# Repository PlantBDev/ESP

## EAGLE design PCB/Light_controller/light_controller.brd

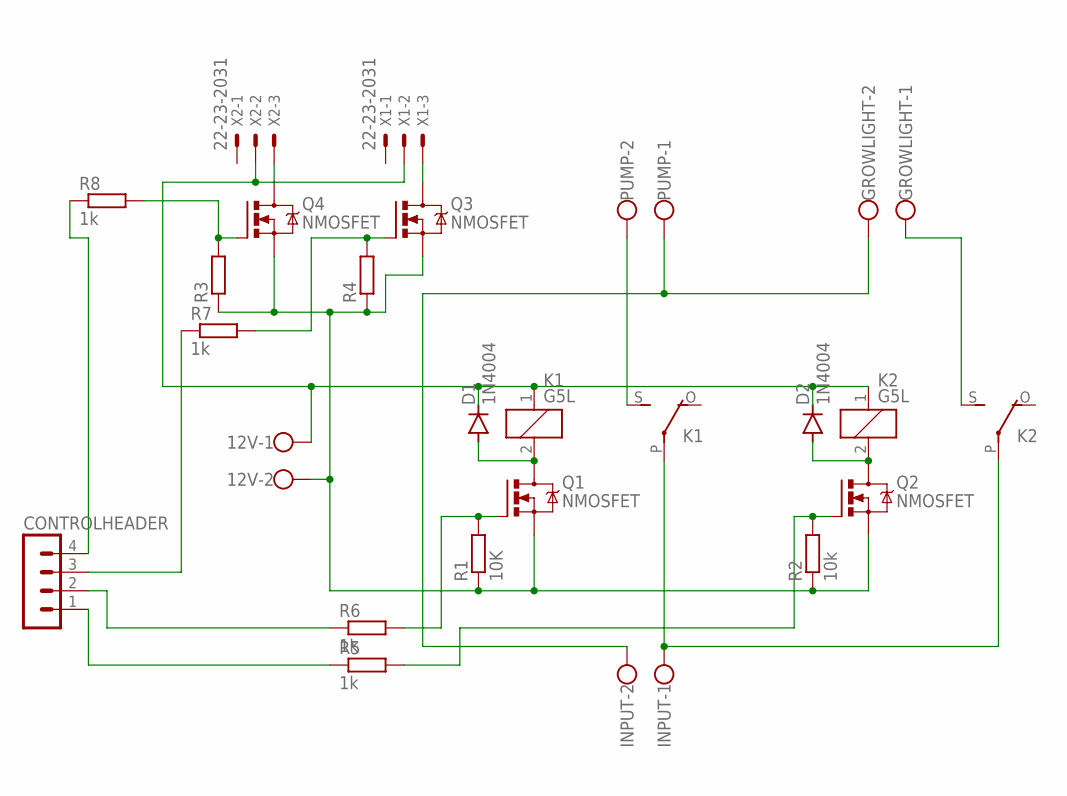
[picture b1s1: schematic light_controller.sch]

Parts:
12V: W237-102
CONTROLHEADER: MA04-1
D1, D2: 1N4004; DO41-10
GROWLIGHT: W237-102
INPUT: W237-102
K1, K2: G5L; G5LE
PUMP: W237-102
Q1, Q2, Q3, Q4: NMOSFET; TO220BV
R1: 10K; 0204/7
R2: 10k; 0204/7
R3, R4: R-EU_0204/7; 0204/7
R5, R6, R7, R8: 1k; 0204/7
X1, X2: 22-23-2031

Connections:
unnamed: D1.A, K1.2, Q1.D
unnamed: INPUT.1, K1.P, K2.P
unnamed: K1.S, PUMP.2
unnamed: GROWLIGHT.2, INPUT.2, PUMP.1
unnamed: 12V.1, D1.C, D2.C, K1.1, K2.1, X1.2, X2.2
unnamed: 12V.2, Q1.S, Q2.S, Q3.S, Q4.S, R1.1, R2.1, R3.1, R4.1
unnamed: Q1.G, R1.2, R6.2
unnamed: D2.A, K2.2, Q2.D
unnamed: Q2.G, R2.2, R5.2
unnamed: Q4.G, R3.2, R8.2
unnamed: GROWLIGHT.1, K2.S
unnamed: Q3.G, R4.2, R7.2
unnamed: CONTROLHEADER.1, R5.1
unnamed: CONTROLHEADER.2, R6.1
unnamed: Q4.D, X2.3
unnamed: Q3.D, X1.3
unnamed: CONTROLHEADER.3, R7.1
unnamed: CONTROLHEADER.4, R8.1

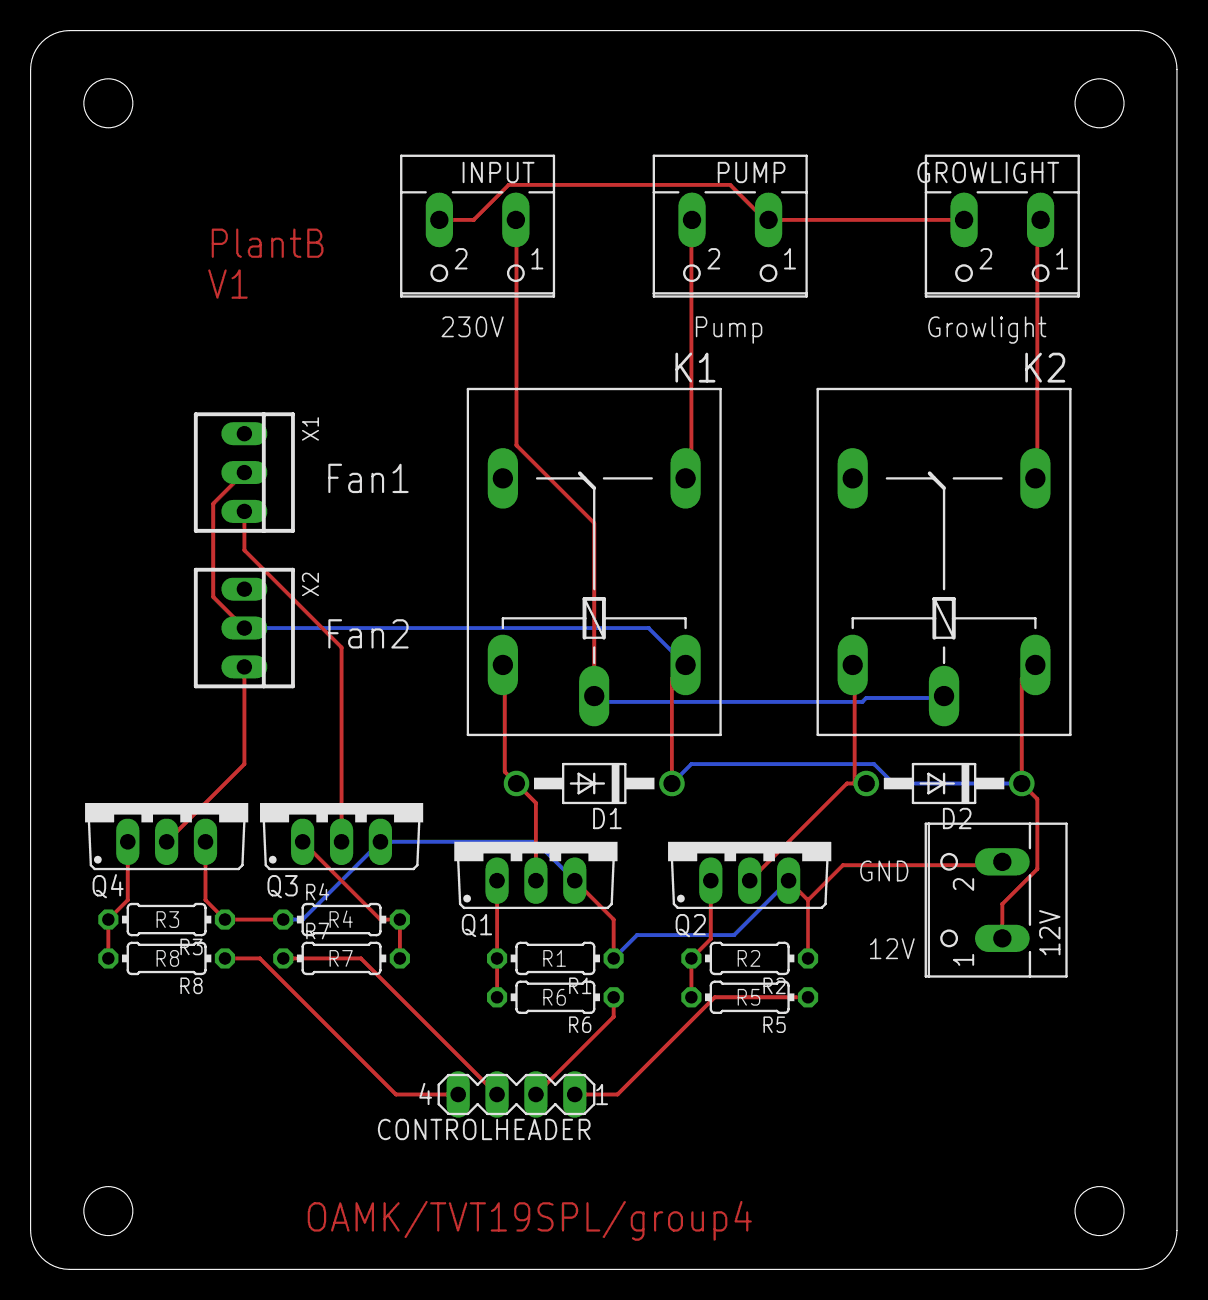
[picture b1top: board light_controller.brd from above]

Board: 2 copper layers, 74.9 x 81.0 mm, 23 parts (0 on the bottom side), 18 nets.

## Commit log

2021-03-23 Create text_print.py
    Python script to display text on the display in the control box. Still very work in progress
2021-03-23 Add files via upload
    This is my fan code
2021-03-23 Modified text_print to be callable
2021-03-23 NodeMainRevision2
    Basic mqtt fuctionality
2021-03-24 Added multi line prints
2021-03-25 Adressable line printing and image
    Added adrressable line printing and the possibility to display images. kukka.jpg is a placeholder logo image.
2021-03-26 WifiManager
    Steal customers wifi name and password and commit dastardly crimes with them
2021-03-31 PCB V1
    version 1 eagle files and gerber for pcb manufacturing
2021-04-07 Create nodeIdentifyv2.ino
    lol
2021-04-07 Added temperature sensor related documents
    Function to read sensors, function to convert data to temperature and octave file and documentation
2021-04-07 Added a function to read temperaturesensors
2021-04-07 Updated nodeMain to revision4
    nodeMain is currently in functioning state
2021-04-10 Add files via upload
    Here is the 3d-models for the plantB body
2021-04-11 Delete potHolderV4_Slim.FCStd
    removed broken model
2021-04-14 Update Waterlevel_sensor_v0.1.ino
    Added some emptyliensd
2021-04-18 NTP clock handler and example main for it
2021-04-18 Added Event timer
    Still very much incomplete
2021-04-19 Progress on event timer and use of sensorRequest
    eventTimer includes still some not so useful input variables
2021-04-21 NodeMainRev6
    6th revision of the main function
2021-04-22 I2C functions
    I2C for both Arduino and Node devices
2021-04-22 fixes to bad code
    yhyy
2021-04-22 various bug fixes
    code is testable, and in working condition
2021-04-22 korjauksia
    misc
2021-04-22 Schematic fetching now works. sort of
    Data is successfully retrieved and stored. Just that my way of converting a string to and int is faulty and needs to be fixed.
2021-04-22 added topicVerification.h
    topicVerification.h + other stuff
2021-04-23 fix
    fix
2021-04-23 payload fix
    fixed payload issues while publishing and subscribing to various topics
2021-04-24 eventTimer added
    added event timer function
2021-04-24 Fixed mqtt payload parsing for schematic data retrieval
    and added zeroing for schematic data to remove previous messages
2021-04-25 Added some comments
    comments, comments, comments, comments, comments, comments, comments, comments, comments, comments, comments, comments, comments, comments, comments, comments, comments, comments, comments, comments,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
2021-04-25 Intense optimization and hardcore bug fixing
2021-04-26 implementing actuator
    Still just a partial implementation
2021-04-26 Fixed crashes
    UwU
2021-04-26 fixed
2021-04-27 Added dangerPublish.h
    publishes danger info whenever it changes
2021-04-27 Hello world!
    Added manual control over eventTimer
2021-04-28 Various bug fixes
    Various fixes and improvements
